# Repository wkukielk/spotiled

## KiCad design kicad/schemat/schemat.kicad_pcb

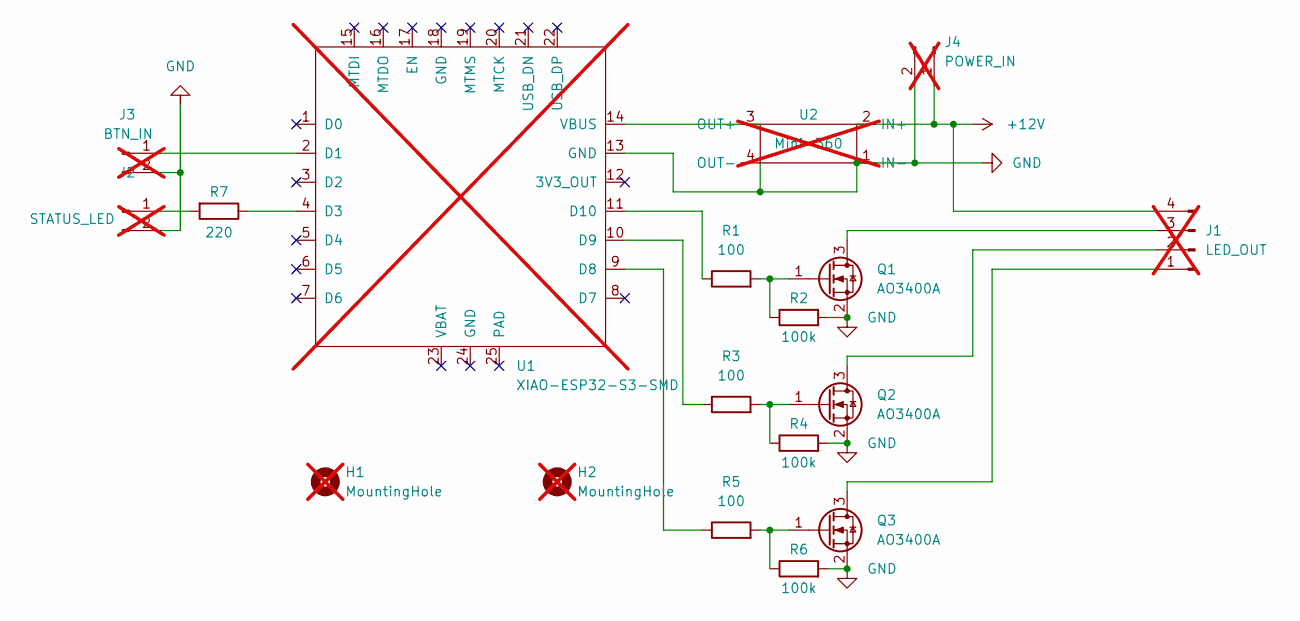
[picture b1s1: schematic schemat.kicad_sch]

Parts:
H1, H2: MountingHole; MountingHole_4.3mm_M4; not fitted
J1: LED_OUT; JST_XH_S4B-XH-A-1_1x04_P2.50mm_Horizontal; not fitted
J2: STATUS_LED; JST_XH_S2B-XH-A-1_1x02_P2.50mm_Horizontal; not fitted
J3: BTN_IN; JST_XH_S2B-XH-A-1_1x02_P2.50mm_Horizontal; not fitted
J4: POWER_IN; JST_XH_S2B-XH-A-1_1x02_P2.50mm_Horizontal; not fitted
Q1, Q2, Q3: AO3400A; SOT-23; LCSC C20917
R1, R3, R5: 100; R_0603_1608Metric; LCSC C22775
R2, R4, R6: 100k; R_0603_1608Metric; LCSC C25803
R7: 220; R_0603_1608Metric; LCSC C22962
U1: XIAO-ESP32-S3-SMD; XIAO-ESP32-S3-DIP; not fitted
U2: Mini-360; Mini-360_Buck_D-SUN; not fitted

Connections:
+12V: J1.4, J4.1, U2.2 (IN+)
GND: J2.2, J3.2, J4.2, Q1.2 (S), Q2.2 (S), Q3.2 (S), R2.2, R4.2, R6.2, U1.13 (GND), U2.1 (IN-), U2.4 (OUT-)
unnamed: J1.1, Q3.3 (D)
unnamed: J1.2, Q2.3 (D)
unnamed: J1.3, Q1.3 (D)
unnamed: J2.1, R7.2
unnamed: J3.1, U1.2 (D1)
unnamed: Q1.1 (G), R1.2, R2.1
unnamed: Q2.1 (G), R3.2, R4.1
unnamed: Q3.1 (G), R5.2, R6.1
unnamed: R7.1, U1.4 (D3)
unnamed: R5.1, U1.9 (D8)
unnamed: R3.1, U1.10 (D9)
unnamed: R1.1, U1.11 (D10)
unnamed: U1.14 (VBUS), U2.3 (OUT+)

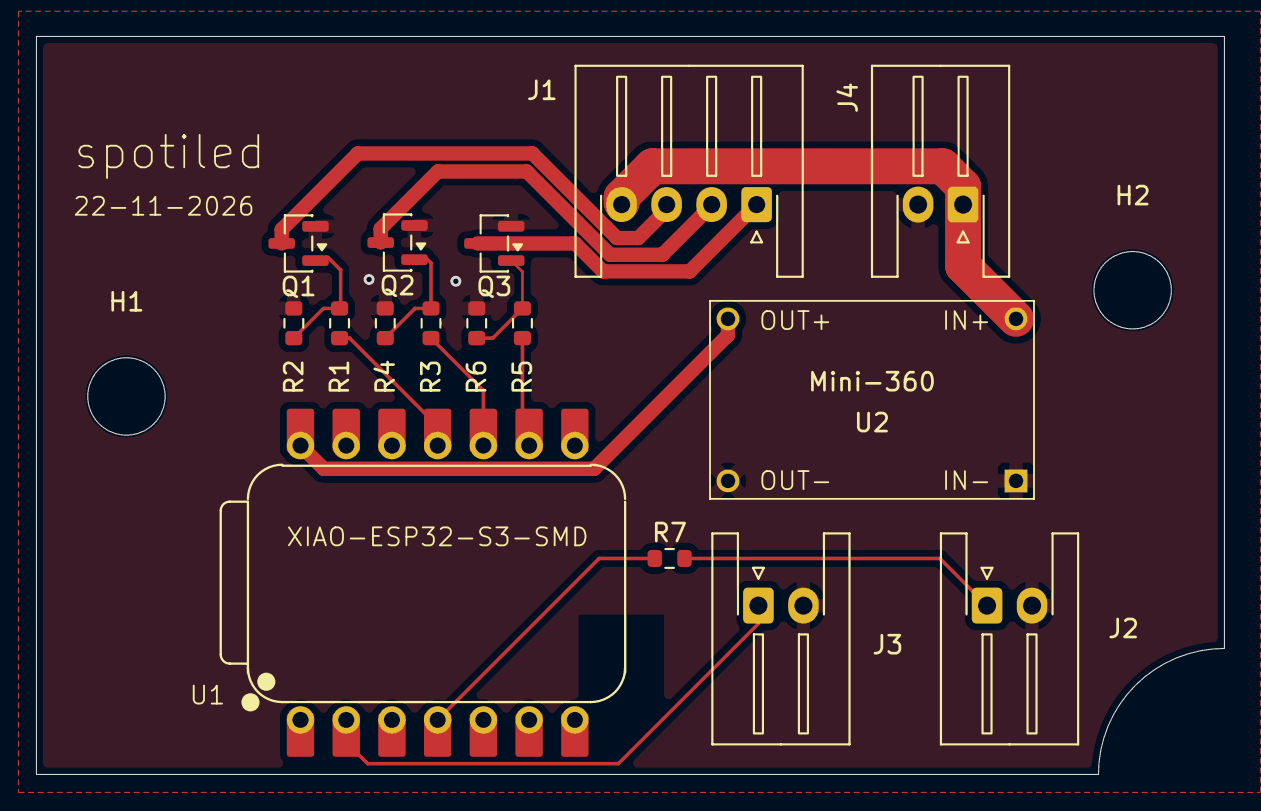
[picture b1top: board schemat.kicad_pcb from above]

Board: 4 copper layers, 66.0 x 41.0 mm, 18 parts (0 on the bottom side), 15 nets.

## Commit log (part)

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2026-01-29 setup backend
2026-01-29 setup nginx
2026-01-29 init esp32 project
2026-01-31 setup firmware's host tests
2026-03-08 pipeline
2026-03-13 ci fix
2026-03-13 config flow
2026-03-13 wifi component
2026-03-13 WiFiEventHandler's cbdata tracks "this" by itself
2026-03-13 HTTPHandler refactor
2026-03-13 one app partition for development
2026-03-13 setup device tests
2026-03-13 fix ht gccoptions fix
2026-03-13 test
2026-03-13 refactor util exceptions
2026-03-13 remove .gitinogre
2026-03-13 mdns wrap
2026-03-13 fix custom nvs partition NVS
2026-03-13 refactor nvs
2026-03-13 add backtrace mock
2026-03-13 ToggleEventHandler refactor
2026-03-13 nvs csv
2026-03-13 PROV_NAME
2026-03-13 add httpclient component
2026-03-13 CharVector
2026-03-13 connects to wifi
2026-03-13 use new exception scheme
2026-03-13 rename ConfigReader to Configurer
2026-03-13 firmware endpoint prototype
2026-03-13 checkpoint
2026-03-13 checkpoint 2
2026-03-13 firmware endpoint
2026-03-13 upgrade to esp idf 5.5
2026-03-13 device unit test mdns
2026-03-13 migrate api_keys
2026-03-13 add devconfig to backend
2026-03-13 move to async backend
2026-03-13 test ota_wrap
2026-03-13 remove api-keys endpoint
2026-03-13 renaming
2026-03-13 ota update request
2026-03-13 move global to i_nterfaces component
2026-03-13 encnvs partition
2026-03-13 add api_keys
2026-03-13 refactor frmware endpoit
2026-03-13 setup backed unit-tests
2026-03-13 move DEV option to Kconfig
2026-03-13 test ota_client
2026-03-13 setup unit-test-app
2026-03-13 mdns config
2026-03-13 test blacklist
2026-03-13 ota wrap
2026-03-13 ota component scaffolding
2026-03-13 setup migraions in docker
2026-03-13 /esp/firmware
2026-03-13 rename to header to Owned-Version
2026-03-13 move ota_wrap, mdns_wrap and wifi_wrap to wrappers component
2026-03-13 blacklist, no tests
2026-03-13 implement URL
2026-03-13 move resolve_url to wifi_manager
2026-03-13 i_mdns, i_wifi, i_ota -> i_interfaces component
2026-03-13 setup migrations
2026-03-13 fix separate Mappers issue
2026-03-13 add authorization to "firmware" endpoint
2026-03-13 unit test backend
2026-03-13 nvs test didn't check custom partition
2026-03-13 fix docs in release version
2026-03-13 update as thread
2026-03-13 move straux, url and time_aux to util component
2026-03-13 mDNSConfig scaffolding
2026-03-13 global mdns
2026-03-13 log config
2026-03-13 resolve local backend correctly
2026-03-13 nvs uses string
2026-03-13 make tests compile
2026-03-13 global macros -> inline functions
2026-03-13 add led component
2026-03-13 fix clang-tidy errors
2026-03-13 remove http_client component
2026-03-13 I_LED interface instead of ledc_ functions
2026-03-13 I_LED and LED
2026-03-13 move scripts and partition files
2026-03-13 gitignore
2026-03-13 using esp-clang image
2026-03-13 CI build mode
2026-03-14 use cache in the workflow
2026-03-20 add flake8
2026-03-20 use custom pepper in test
2026-03-20 backend job and action version update
2026-03-21 script for api key generation
2026-03-21 proper app cleanup
2026-05-19 backend test script
2026-05-19 Queue<T>
2026-05-19 runtime state machine structure
2026-05-24 queue send_front
2026-05-24 test filtering
2026-05-24 runtime, renaming
2026-05-24 test queue
2026-05-24 no reconnect state
2026-05-26 tidying up
2026-05-26 example esp config
2026-05-26 rename aux
2026-05-26 all backend config in yaml, no env
2026-05-26 make it compile
2026-05-26 update *ignore
2026-05-27 no state in Runtime
2026-05-28 refactor... in progress
2026-05-28 ServerThread
2026-05-28 runs again
2026-05-28 ws server runs
2026-05-30 httpd config correct passing
2026-05-30 claude refactor led
2026-05-30 wsserver tests (AI generated)
2026-05-31 testing led
2026-06-01 I_DftEventLoop
2026-06-03 LED refactor cd
2026-06-04 Toggle
2026-06-04 app compiled
2026-06-04 tests succeed
2026-06-07 WiFiEventHandler refactor
2026-06-08 works
2026-06-11 Handle<WiFi>
2026-06-22 setup controller
2026-06-23 add dom_color c++ library
2026-06-23 print rgb
2026-06-23 anyway anyhow
2026-06-24 test with mock
2026-06-24 testing SongPipeline
2026-06-24 add server
2026-06-26 app setup refactor
2026-06-27 test wifi manager
2026-06-27 get rid of state machine in ServerThread
2026-06-27 move constructors
2026-06-28 server handles "fade" command
2026-06-28 i_nterface classes (wifi, dfteloop) hold no resource
2026-06-28 ws server refactor
2026-06-28 fix 100% cpu bug in controller
2026-06-30 use mercury
2026-06-30 SongPipelineError
